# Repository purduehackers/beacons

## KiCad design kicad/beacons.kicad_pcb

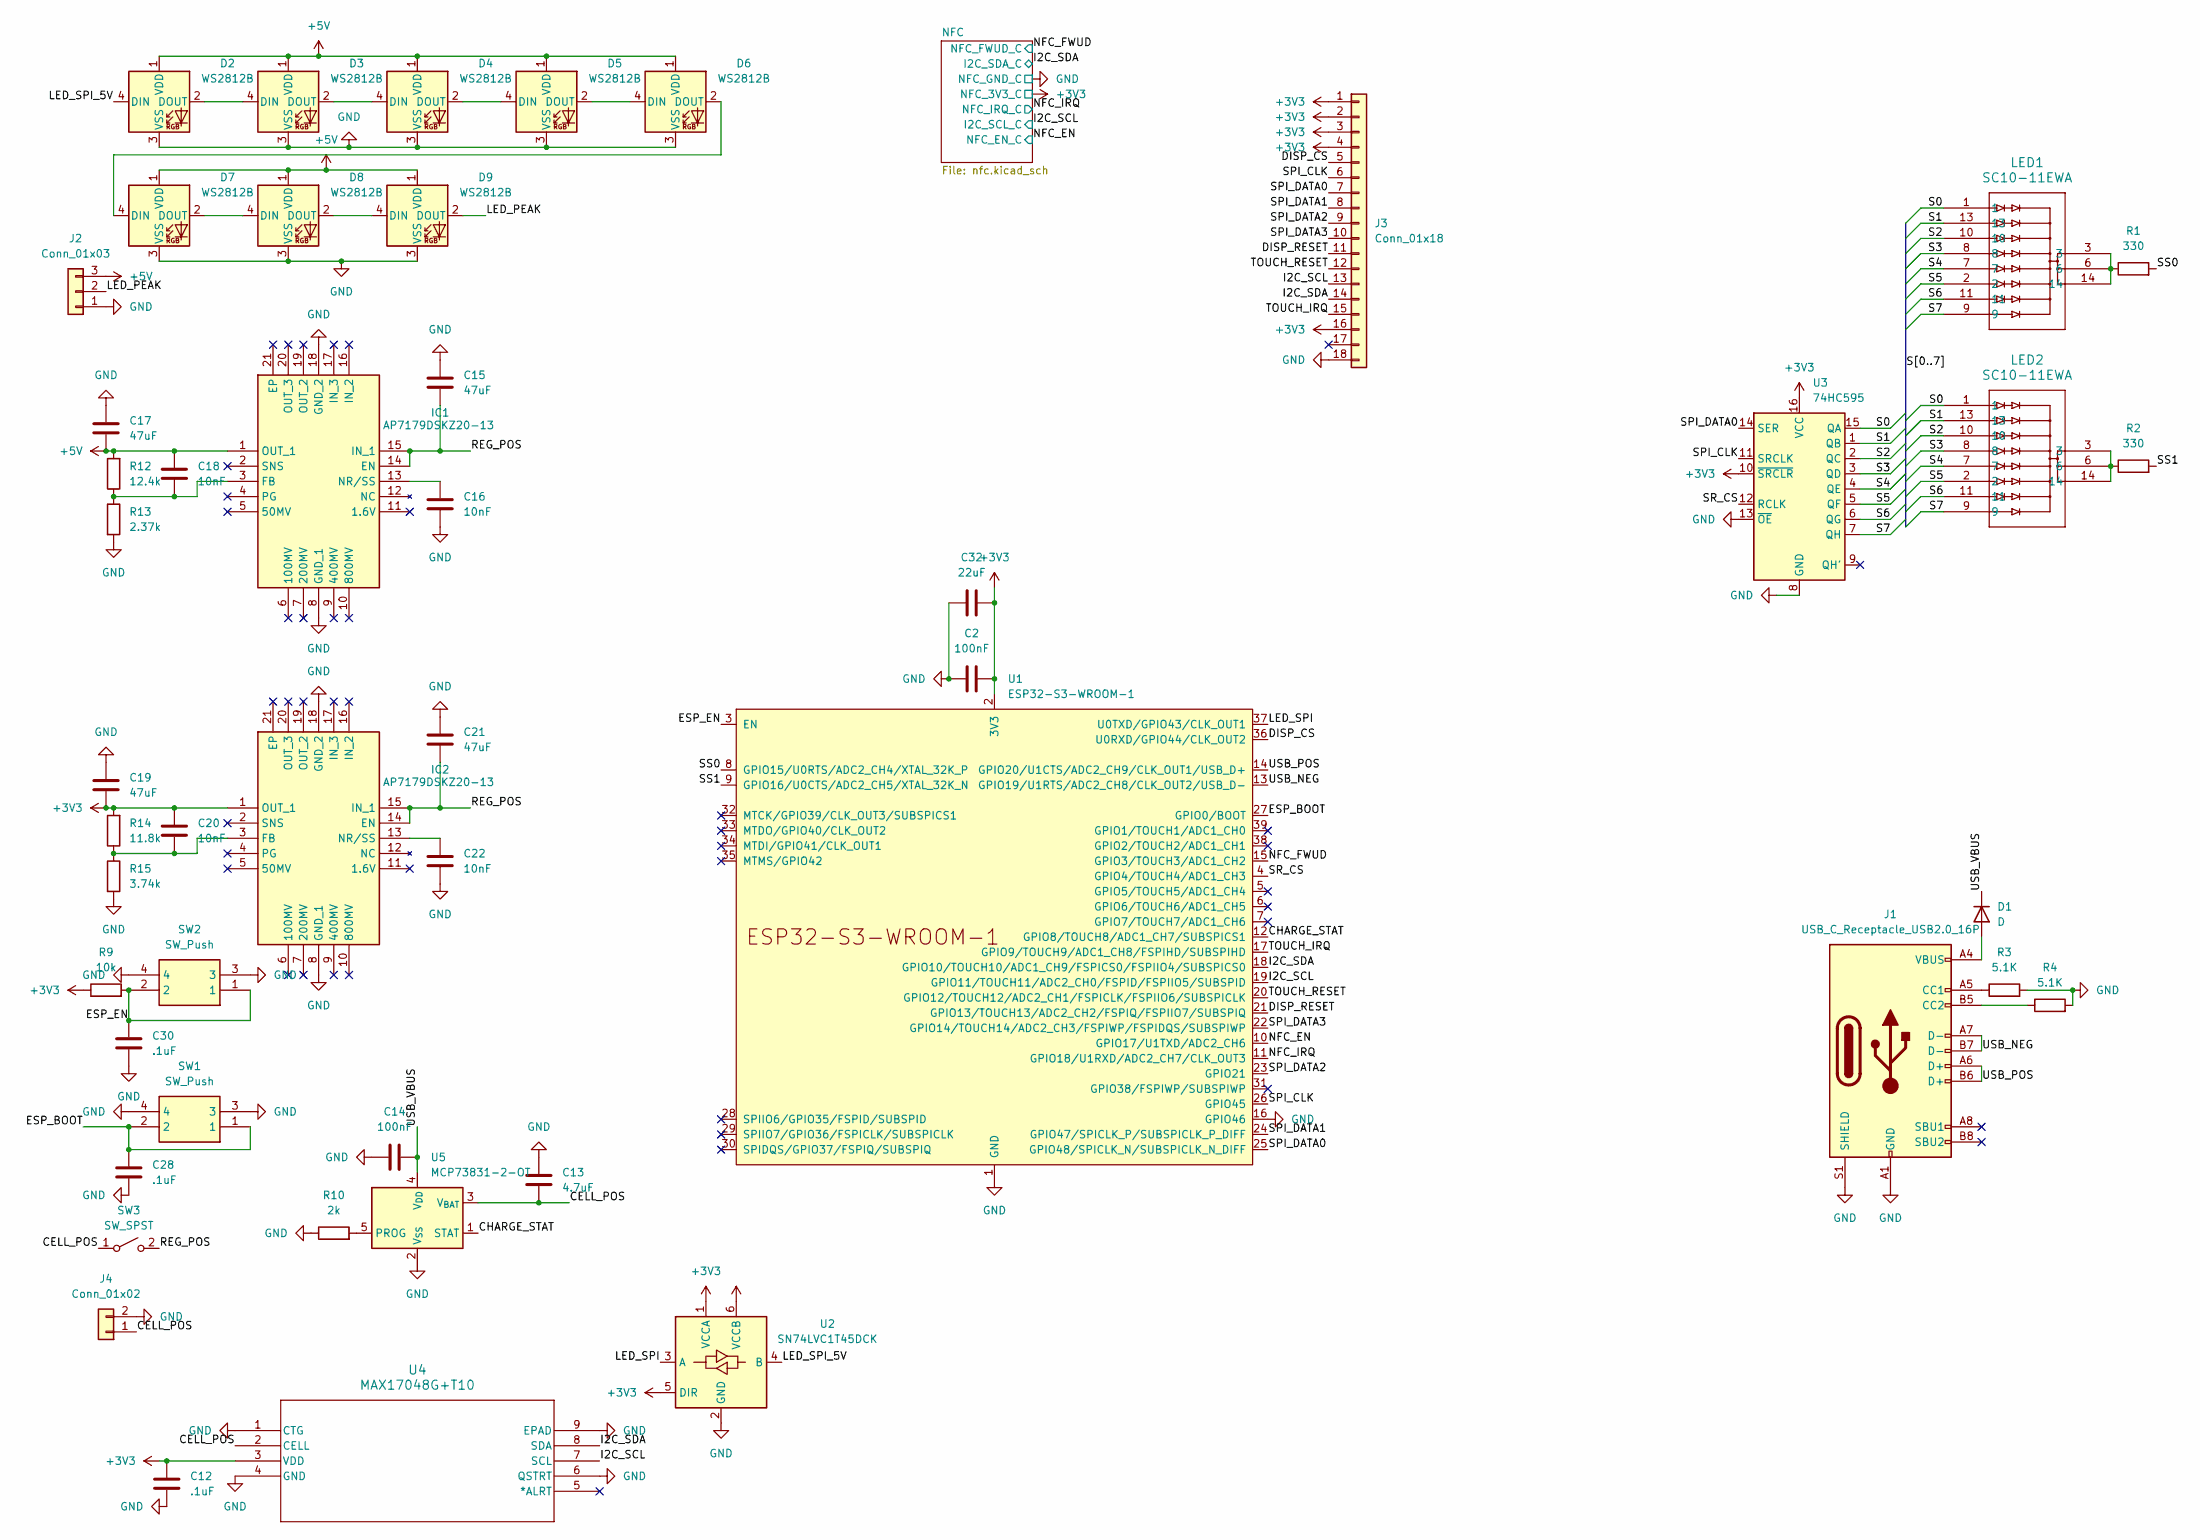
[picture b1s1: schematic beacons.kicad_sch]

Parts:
C2, C14: 100nF; C_0402_1005Metric
C12, C28, C30: .1uF; C_0402_1005Metric
C13: 4.7uF; C_0402_1005Metric
C15, C17, C19, C21: 47uF; C_0402_1005Metric
C16, C18, C20, C22: 10nF; C_0402_1005Metric
C32: 22uF; C_0402_1005Metric
D1: D; D_SOD-323
D2, D3, D4, D5, D6, D7, D8, D9: WS2812B; LED_WS2812B_PLCC4_5.0x5.0mm_P3.2mm
IC1, IC2: AP7179DSKZ20-13; QFN50P350X350X80-21N-D; Manufacturer_Part_Number AP7179DSKZ20-13
J1: USB_C_Receptacle_USB2.0_16P; USB_C_Receptacle_GCT_USB4105-xx-A_16P_TopMnt_Horizontal
J2: Conn_01x03; JST_PH_B3B-PH-K_1x03_P2.00mm_Vertical
J3: Conn_01x18; DisplayConnector
J4: Conn_01x02; AMASS_XT30UPB-M_1x02_P5.0mm_Vertical
LED1, LED2: SC10-11EWA; SC10-11EWA_KNB
R1, R2: 330; R_0402_1005Metric
R3, R4: 5.1K; R_0402_1005Metric
R9: 10k; R_0402_1005Metric
R10: 2k; R_0402_1005Metric
R12: 12.4k; R_0402_1005Metric
R13: 2.37k; R_0402_1005Metric
R14: 11.8k; R_0402_1005Metric
R15: 3.74k; R_0402_1005Metric
SW1, SW2: SW_Push; SMT_4.2X3.2_; Manufacturer_Part_Number SKRPACE010; Mouser Part Number 688-SKRPACE010
SW3: SW_SPST; AMASS_XT30UPB-M_1x02_P5.0mm_Vertical
U1: ESP32-S3-WROOM-1
U2: SN74LVC1T45DCK; SOT-363_SC-70-6
U3: 74HC595; SSOP-16_5.3x6.2mm_P0.65mm
U4: MAX17048G+T10; 21-0168E_T822-3_MXM
U5: MCP73831-2-OT; SOT-23-5

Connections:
+3V3: C2.2, C12.1, C19.2, C20.1, C32.2, IC2.1 (OUT_1), J3.1, J3.2, J3.3, J3.4, J3.16, R9.1, R14.2, U1.2 (3V3), U2.1 (VCCA), U2.5 (DIR), U3.10 (~SRCLR), U3.16 (VCC), U4.3 (VDD); also elsewhere on the board
+5V: C17.2, C18.1, D2.1 (VDD), D3.1 (VDD), D4.1 (VDD), D5.1 (VDD), D6.1 (VDD), D7.1 (VDD), D8.1 (VDD), D9.1 (VDD), IC1.1 (OUT_1), J2.3, R12.2, U2.6 (VCCB)
/CELL_POS: C13.2, J4.1, SW3.1 (A), U4.2 (CELL), U5.3 (V_{BAT})
/CHARGE_STAT: U1.12 (GPIO8/TOUCH8/ADC1_CH7/SUBSPICS1), U5.1 (STAT)
/DISP_CS: J3.5, U1.36 (U0RXD/GPIO44/CLK_OUT2)
/DISP_RESET: J3.11, U1.21 (GPIO13/TOUCH13/ADC2_CH2/FSPIQ/FSPIIO7/S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)
/ESP_BOOT: C28.1, SW1.1, SW1.2, U1.27 (GPIO0/BOOT)
/ESP_EN: C30.1, R9.2, SW2.1, SW2.2, U1.3 (EN)
/I2C_SCL: J3.13, U1.19 (GPIO11/TOUCH11/ADC2_CH0/FSPID/FSPIIO5/S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), U4.7 (SCL); also elsewhere on the board
/I2C_SDA: J3.14, U1.18 (GPIO10/TOUCH10/ADC1_CH9/FSPICS0/FSPIIO4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), U4.8 (SDA); also elsewhere on the board
/LED_PEAK: D9.2 (DOUT), J2.2
/LED_SPI: U1.37 (U0TXD/GPIO43/CLK_OUT1), U2.3 (A)
/LED_SPI_5V: D2.4 (DIN), U2.4 (B)
/NFC_EN: U1.10 (GPIO17/U1TXD/ADC2_CH6); also elsewhere on the board
/NFC_FWUD: U1.15 (GPIO3/TOUCH3/ADC1_CH2); also elsewhere on the board
/NFC_IRQ: U1.11 (GPIO18/U1RXD/ADC2_CH7/CLK_OUT3); also elsewhere on the board
/REG_POS: C15.2, C21.2, IC1.14 (EN), IC1.15 (IN_1), IC2.14 (EN), IC2.15 (IN_1), SW3.2 (B)
/S0: LED1.1, LED2.1, U3.15 (QA)
/S1: LED1.13, LED2.13, U3.1 (QB)
/S2: LED1.10, LED2.10, U3.2 (QC)
/S3: LED1.8, LED2.8, U3.3 (QD)
/S4: LED1.7, LED2.7, U3.4 (QE)
/S5: LED1.2, LED2.2, U3.5 (QF)
/S6: LED1.11, LED2.11, U3.6 (QG)
/S7: LED1.9, LED2.9, U3.7 (QH)
/SPI_CLK: J3.6, U1.26 (GPIO45), U3.11 (SRCLK)
/SPI_DATA0: J3.7, U1.25 (GPIO48/SPICLK_N/SUBSPICLK_N_DIFF), U3.14 (SER)
/SPI_DATA1: J3.8, U1.24 (GPIO47/SPICLK_P/SUBSPICLK_P_DIFF)
/SPI_DATA2: J3.9, U1.23 (GPIO21)
/SPI_DATA3: J3.10, U1.22 (GPIO14/TOUCH14/ADC2_CH3/FSPIWP/FSPIDQS/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)
/SR_CS: U1.4 (GPIO4/TOUCH4/ADC1_CH3), U3.12 (RCLK)
/SS0: R1.2, U1.8 (GPIO15/U0RTS/ADC2_CH4/XTAL_32K_P)
/SS1: R2.2, U1.9 (GPIO16/U0CTS/ADC2_CH5/XTAL_32K_N)
/TOUCH_IRQ: J3.15, U1.17 (GPIO9/TOUCH9/ADC1_CH8/FSPIHD/SUBSPIHD)
/TOUCH_RESET: J3.12, U1.20 (GPIO12/TOUCH12/ADC2_CH1/FSPICLK/FSPIIO6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)
/USB_NEG: J1.A7 (D-), J1.B7 (D-), U1.13 (GPIO19/U1RTS/ADC2_CH8/CLK_OUT2/USB_D-)
/USB_POS: J1.A6 (D+), J1.B6 (D+), U1.14 (GPIO20/U1CTS/ADC2_CH9/CLK_OUT1/USB_D+)
/USB_VBUS: C14.2, D1.1 (K), U5.4 (V_{DD})
GND: C2.1, C12.2, C13.1, C14.1, C15.1, C16.1, C17.1, C19.1, C21.1, C22.1, C28.2, C30.2, C32.1, D2.3 (VSS), D3.3 (VSS), D4.3 (VSS), D5.3 (VSS), D6.3 (VSS), D7.3 (VSS), D8.3 (VSS), D9.3 (VSS), IC1.8 (GND_1), IC1.18 (GND_2), IC2.8 (GND_1), IC2.18 (GND_2), J1.A1 (GND), J1.A12 (GND), J1.B1 (GND), J1.B12 (GND), J1.S1 (SHIELD), J2.1, J3.18, J4.2, R3.2, R4.2, R10.1, R13.2, R15.2, SW1.3, SW1.4, SW2.3, SW2.4, U1.1 (GND), U1.16 (GPIO46), U1.40 (GND), U1.41 (GND), U2.2 (GND), U3.8 (GND), U3.13 (~OE), U4.1 (CTG), U4.4 (GND), U4.6 (QSTRT), U4.9 (EPAD), U5.2 (V_{SS}); also elsewhere on the board
unnamed: D1.2 (A), J1.A4 (VBUS), J1.A9 (VBUS), J1.B4 (VBUS), J1.B9 (VBUS)
unnamed: D2.2 (DOUT), D3.4 (DIN)
unnamed: D3.2 (DOUT), D4.4 (DIN)
unnamed: D4.2 (DOUT), D5.4 (DIN)
unnamed: D5.2 (DOUT), D6.4 (DIN)
unnamed: D6.2 (DOUT), D7.4 (DIN)
unnamed: D7.2 (DOUT), D8.4 (DIN)
unnamed: D8.2 (DOUT), D9.4 (DIN)
unnamed: C18.2, IC1.3 (FB), R12.1, R13.1
unnamed: C16.2, IC1.13 (NR/SS)
unnamed: C20.2, IC2.3 (FB), R14.1, R15.1
unnamed: C22.2, IC2.13 (NR/SS)
unnamed: J1.A5 (CC1), R3.1
unnamed: J1.B5 (CC2), R4.1
unnamed: LED1.3, LED1.6, LED1.14, R1.1
unnamed: LED2.3, LED2.6, LED2.14, R2.1
unnamed: R10.2, U5.5 (PROG)

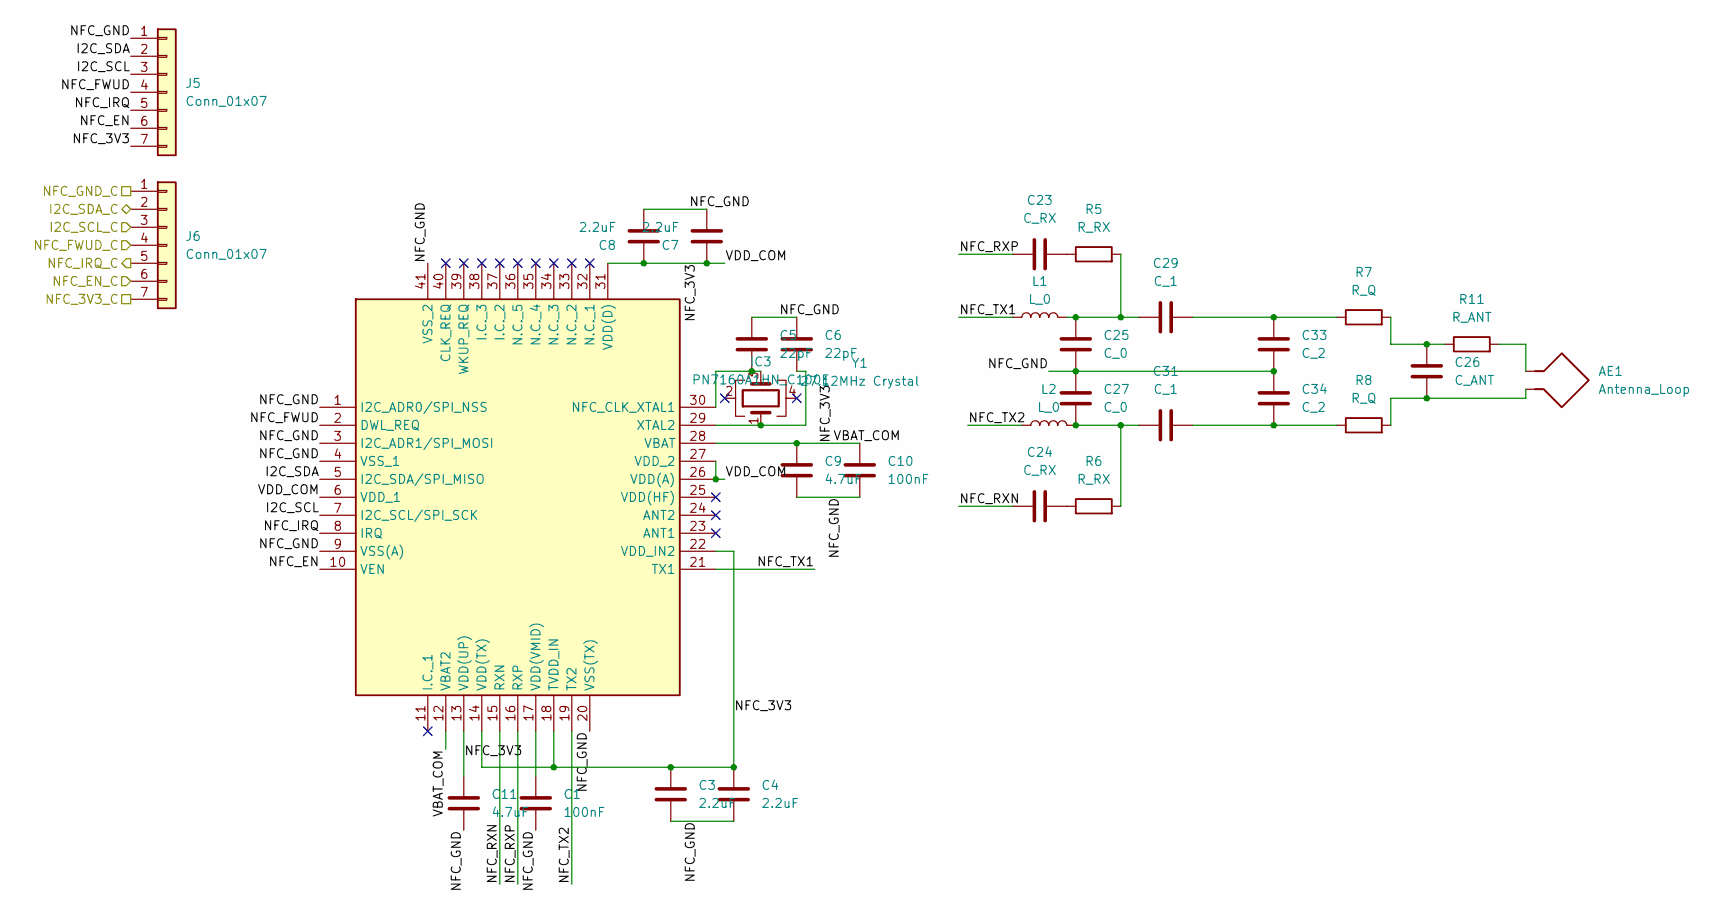
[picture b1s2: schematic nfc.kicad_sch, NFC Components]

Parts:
AE1: Antenna_Loop; NFC
C1, C10: 100nF; C_0402_1005Metric
C3, C4, C7, C8: 2.2uF; C_0402_1005Metric
C5, C6: 22pF; C_0402_1005Metric
C9, C11: 4.7uF; C_0402_1005Metric
C23, C24: C_RX; C_0402_1005Metric
C25, C27: C_0; C_0402_1005Metric
C26: C_ANT; C_0402_1005Metric
C29, C31: C_1; C_0402_1005Metric
C33, C34: C_2; C_0402_1005Metric
IC3: PN7160A1HN_C100E; QFN50P600X600X100-41N-D; Manufacturer_Part_Number PN7160A1HN/C100E; Mouser Part Number 771-PN7160A1HN/C100E
J5, J6: Conn_01x07; JST_PH_B7B-PH-K_1x07_P2.00mm_Vertical
L1, L2: L_0; L_0402_1005Metric
R5, R6: R_RX; R_0402_1005Metric
R7, R8: R_Q; R_0402_1005Metric
R11: R_ANT; R_0402_1005Metric
Y1: 27.12MHz Crystal; Crystal_SMD_2016-4Pin_2.0x1.6mm

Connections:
+3V3: J6.7; also elsewhere on the board
/I2C_SCL: J6.3; also elsewhere on the board
/I2C_SDA: J6.2; also elsewhere on the board
/NFC/I2C_SCL: IC3.7 (I2C_SCL/SPI_SCK), J5.3
/NFC/I2C_SDA: IC3.5 (I2C_SDA/SPI_MISO), J5.2
/NFC/NFC_EN: IC3.10 (VEN), J5.6
/NFC/NFC_FWUD: IC3.2 (DWL_REQ), J5.4
/NFC/NFC_GND: C1.2, C3.2, C4.2, C5.1, C6.1, C7.2, C8.2, C9.2, C10.2, C11.2, C25.2, C27.1, C33.2, C34.1, IC3.1 (I2C_ADR0/SPI_NSS), IC3.3 (I2C_ADR1/SPI_MOSI), IC3.4 (VSS_1), IC3.9 (VSS(A)), IC3.20 (VSS(TX)), IC3.41 (VSS_2), J5.1
/NFC/NFC_IRQ: IC3.8 (IRQ), J5.5
/NFC/NFC_RXN: C24.1, IC3.15 (RXN)
/NFC/NFC_RXP: C23.1, IC3.16 (RXP)
/NFC/NFC_TX1: IC3.21 (TX1), L1.1
/NFC/NFC_TX2: IC3.19 (TX2), L2.1
/NFC_EN: J6.6; also elsewhere on the board
/NFC_FWUD: J6.4; also elsewhere on the board
/NFC_IRQ: J6.5; also elsewhere on the board
GND: J6.1; also elsewhere on the board
unnamed: AE1.1, R11.2
unnamed: AE1.2, C26.2, R8.2
unnamed: C23.2, R5.1
unnamed: C24.2, R6.1
unnamed: C25.1, C29.1, L1.2, R5.2
unnamed: C26.1, R7.2, R11.1
unnamed: C27.2, C31.1, L2.2, R6.2
unnamed: C29.2, C33.1, R7.1
unnamed: C31.2, C34.2, R8.1
unnamed: C5.2, IC3.30 (NFC_CLK_XTAL1), Y1.3
unnamed: C1.1, IC3.17 (VDD(VMID))
unnamed: C6.2, IC3.29 (XTAL2), Y1.1

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
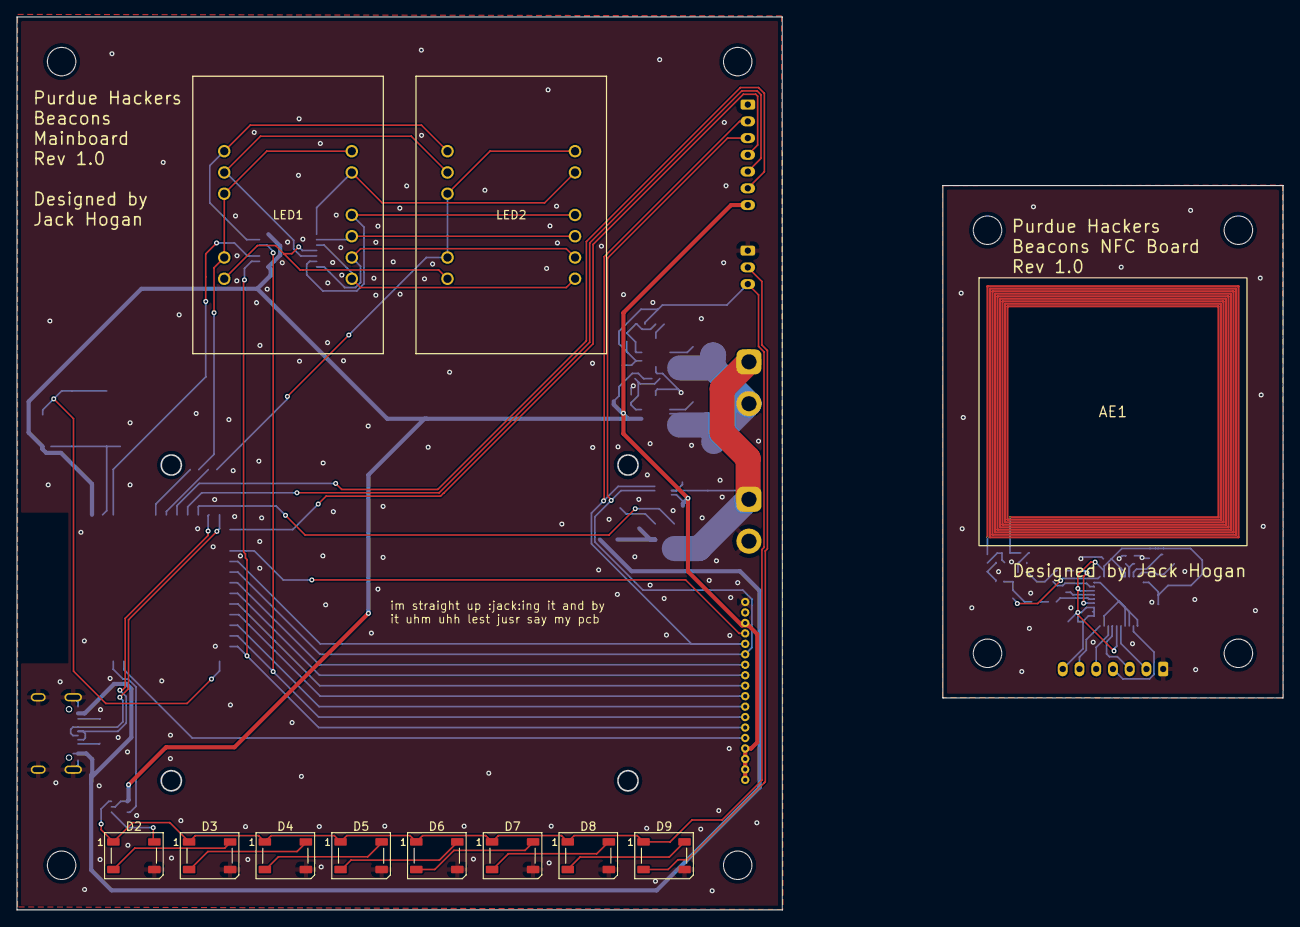
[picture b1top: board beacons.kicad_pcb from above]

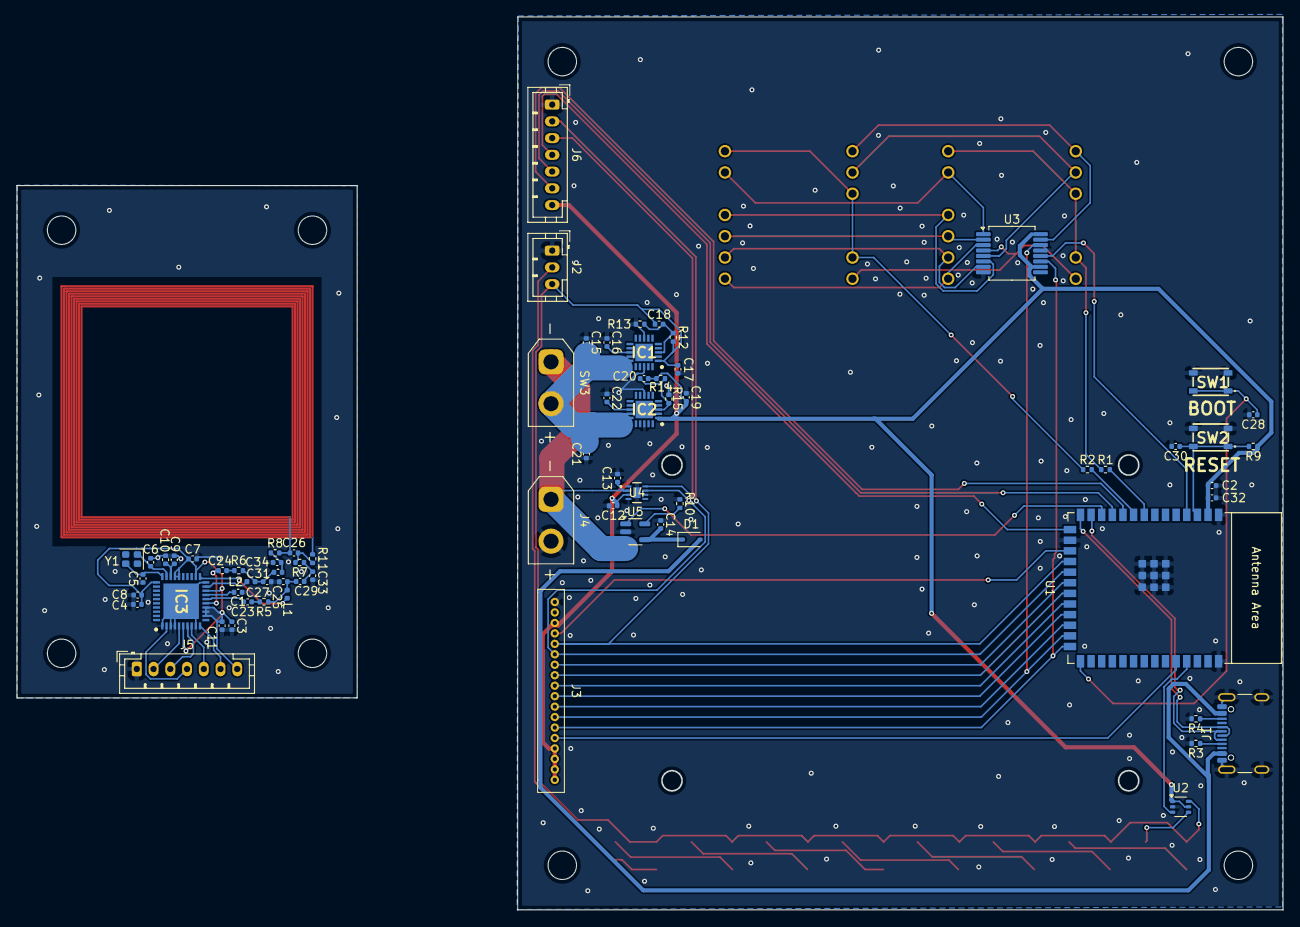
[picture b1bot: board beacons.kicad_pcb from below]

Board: 2 copper layers, 151.1 x 106.5 mm, 81 parts (70 on the bottom side), 80 nets.

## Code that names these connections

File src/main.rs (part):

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    mut wifi: AsyncWifi<EspWifi<'static>>,
    mut amoled: Rm690B0<'static, std::sync::Arc<SpiDriver<'static>>>,
    mut touch: Ft6336<I2c>,
    mut touch_irq: PinDriver<'static, AnyInputPin, Input>,
    mut nfc: Pn532<
        I2CInterfaceWithIrq<I2c, InfallibleDriver<PinDriver<'static, AnyInputPin, Input>>>,
        (),
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
    let driver = SpiDriver::new_quad(
        peripherals.spi3,
        peripherals.pins.gpio18,
        peripherals.pins.gpio17,
        peripherals.pins.gpio16,
        peripherals.pins.gpio14,
        peripherals.pins.gpio8,
        &DriverConfig::new(),
    )
    .expect("qspi driver");
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    let displays = {
        // let data = PinDriver::output(peripherals.pins.gpio5.downgrade_output()).expect("data pin");
        // let latch = PinDriver::output(peripherals.pins.gpio6.downgrade_output()).expect("data pin");
        // let clk = PinDriver::output(peripherals.pins.gpio9.downgrade_output()).expect("data pin");
        let low_digit = PinDriver::output(peripherals.pins.gpio10).expect("low digit");
        let high_digit = PinDriver::output(peripherals.pins.gpio11).expect("low digit");

        let spi = SpiDeviceDriver::new(
            driver.clone(),
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    let amoled = {
        let qspi = SpiDeviceDriver::new(
            driver.clone(),
            Some(peripherals.pins.gpio13),
            &Config::default()
                .data_mode(MODE_3)
                .duplex(Duplex::Half)
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
    let i2c = I2cDriver::new(
        peripherals.i2c0,
        peripherals.pins.gpio3,
        peripherals.pins.gpio4,
        &I2cConfig::default().baudrate(Hertz(100_000)),
    )
    .expect("i2c");
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        std::thread::sleep(std::time::Duration::from_millis(5));
        reset.set_high().expect("reset high");

        let mut irq = PinDriver::input(peripherals.pins.gpio9.downgrade_input()).expect("irq");
        irq.set_interrupt_type(esp_idf_svc::hal::gpio::InterruptType::NegEdge)
            .expect("set irq mode");

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        )
        .expect("valid spi");

        let irq = PinDriver::input(peripherals.pins.gpio12.downgrade_input()).expect("irq pin");

        let interface = pn532::i2c::I2CInterfaceWithIrq {
            i2c: bus.acquire_i2c(),
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            let leds = {
                let driver = SpiDriver::new_without_sclk(
                    peripherals.spi2,
                    peripherals.pins.gpio15,
                    None::<AnyInputPin>,
                    &DriverConfig::new(),
                )
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
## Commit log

2024-12-28 Initial
2024-12-28 Test
2024-12-29 Add proposal
2024-12-30 Write proposal
2025-01-04 Added net and hardware code
2025-01-04 LEDs and first flash
2025-01-04 Maybe fix CI
2025-01-04 Copy Sign CI
2025-01-06 Added seven segment display
2025-03-03 Add nfc reminder
2025-07-08 Worked on display
2025-07-11 Code compiles on rust 1.88
2025-07-12 Initial display code
2025-07-12 Support hexadecimal for seven segment
2025-07-12 TE off
2025-07-13 Lots of display stuff
2025-07-13 Testing code for display
2025-07-25 Setup NFC and moved shift register to SPI
2025-07-25 Switch to I2C for NFC, hookup touch panel
2025-07-25 Touchscreen
2025-07-27 Start work on PCB
2025-07-27 More pcb work
2025-07-31 Tons of stuff
2025-08-02 Routing and RF
2025-08-02 First revision
2025-08-03 Added level shifter
2025-08-03 Added NFC enable pin
2025-09-02 Move nfc antenna away from traces
2025-09-06 Refactor and added website things
2025-09-06 Start pcb review
